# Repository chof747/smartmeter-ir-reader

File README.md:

## Smartmeter IR Reader/Writer

This is an implementation of the smart reader concept created by [volkszaehler.org](https://wiki.volkszaehler.org/hardware/controllers/ir-schreib-lesekopf-ttl-ausgang).

It has been modified as follows:

- Replaced 13k resistors by 10k (as I have a lot of them in stock)
- Added an RJ11 connector with 4 pins as a connector to the microcontroller unit

This board is intended to interface with a Microcontroller unit via an RJ11 connector.

## Schematic & Board Layout

## Revision History:
- **v1.0**: Initial version (Produced: 19.08.2023; not assembled)
- **v1.1**: Corrected RJ11 socket connector (Produced: 19.09.2023; First Assembly: 06.10.2023))
- **v1.2**: Corrected misorientation of Q1/Q2 transistor pins, Board cutout and added Pin descriptions (Produced 15.10.2023; Asembled: 10.11.2023 - successfully)

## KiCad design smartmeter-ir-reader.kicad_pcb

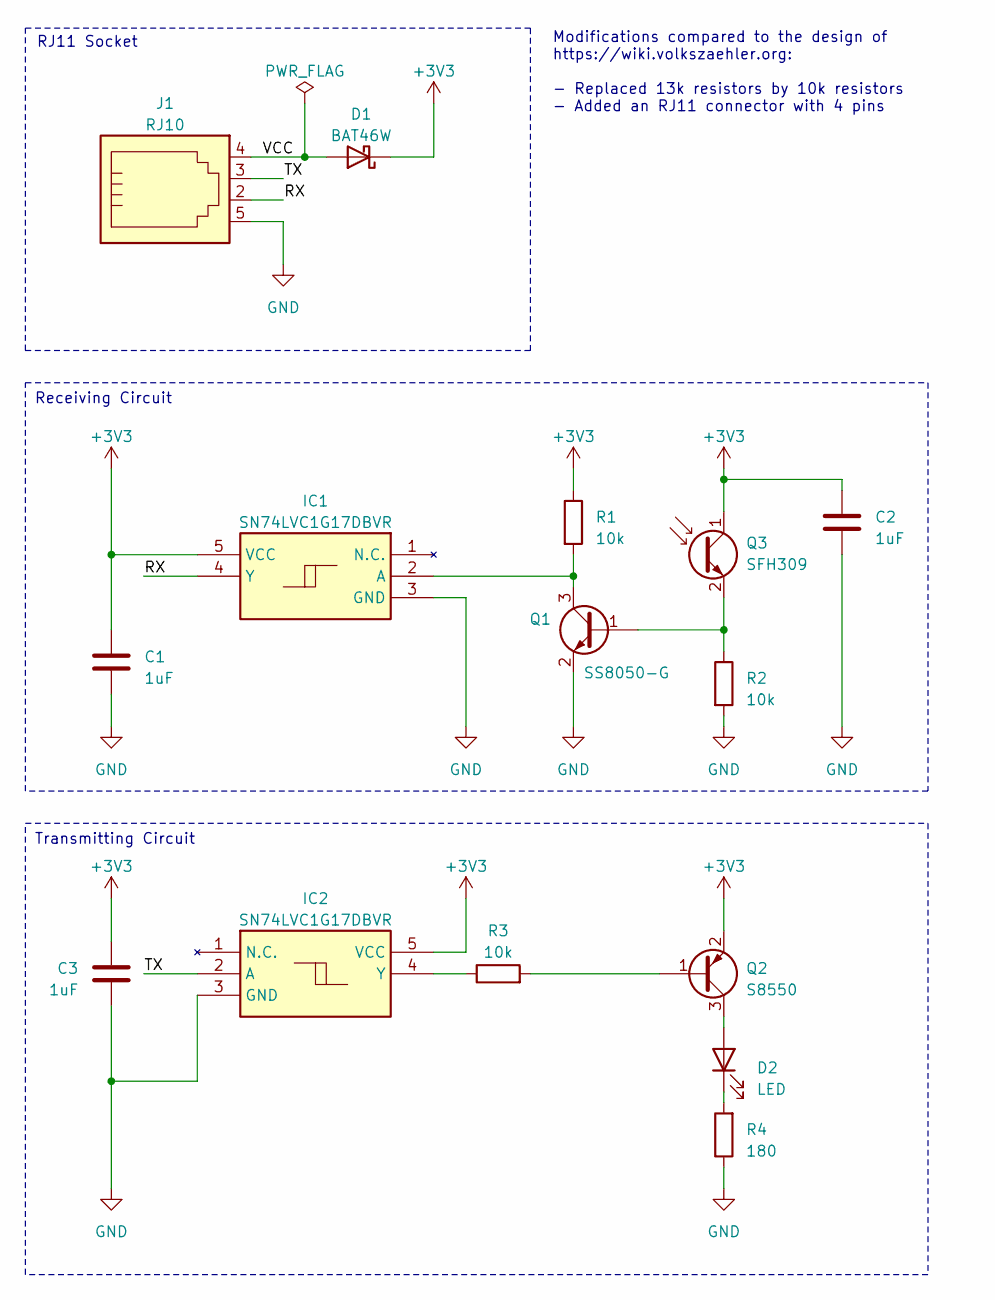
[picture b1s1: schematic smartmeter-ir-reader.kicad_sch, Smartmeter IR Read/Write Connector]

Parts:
C1, C2, C3: 1uF; C_0603_1608Metric_Pad1.08x0.95mm_HandSolder
D1: BAT46W; D_SOD-123
D2: LED; LED_D3.0mm_Clear
IC1, IC2: SN74LVC1G17DBVR; SOT95P270X145-5N; Manufacturer_Part_Number SN74LVC1G17DBVR; Mouser Part Number 595-SN74LVC1G17DBVR
J1: RJ10; RJ12_Amphenol_54601
Q1: SS8050-G; SOT-23
Q2: S8550; SOT-23
Q3: SFH309; LED_D3.0mm_Clear
R1, R2, R3: 10k; R_0603_1608Metric_Pad0.98x0.95mm_HandSolder
R4: 180; R_0603_1608Metric_Pad0.98x0.95mm_HandSolder

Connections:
+3V3: C1.1, C2.1, C3.1, D1.1 (K), IC1.5 (VCC), IC2.5 (VCC), Q2.2 (E), Q3.1 (C), R1.1
/RX: IC1.4 (Y), J1.2
/TX: IC2.2 (A), J1.3
/VCC: D1.2 (A), J1.4
GND: C1.2, C2.2, C3.2, IC1.3 (GND), IC2.3 (GND), J1.5, Q1.2 (E), R2.2, R4.1
unnamed: D2.2 (A), Q2.3 (C)
unnamed: D2.1 (K), R4.2
unnamed: IC1.2 (A), Q1.3 (C), R1.2
unnamed: IC2.4 (Y), R3.1
unnamed: Q1.1 (B), Q3.2 (E), R2.1
unnamed: Q2.1 (B), R3.2

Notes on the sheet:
Receiving Circuit
Transmitting Circuit
Modifications compared to the design of https://wiki.volkszaehler.org: - Replaced 13k resistors by 10k resistors - Added an RJ11 connector with 4 pins
RJ11 Socket

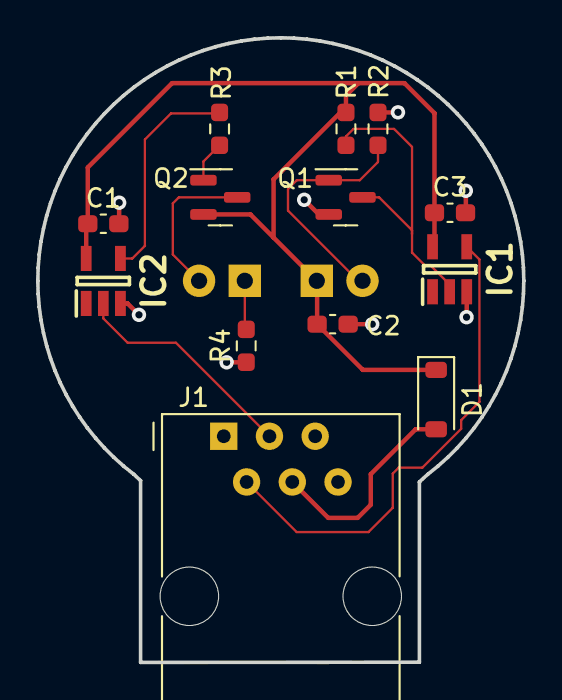
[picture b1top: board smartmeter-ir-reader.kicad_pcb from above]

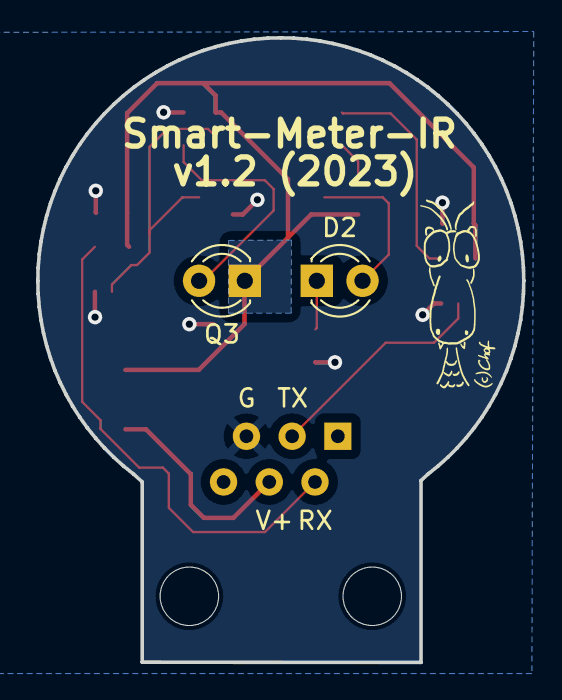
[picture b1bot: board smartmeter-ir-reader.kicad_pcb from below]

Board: 2 copper layers, 27.0 x 34.7 mm, 15 parts (2 on the bottom side), 11 nets.

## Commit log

2023-07-28 Initial commit including docs for volkszaehler pcb and schematics
2023-08-03 Initial version
2023-08-19 Initial version Revision 1.0
2023-09-15 corrected RJ12 socket Connector
2023-10-06 First Assembly
2023-10-11 Reformatted schematic
2023-10-11 Added board drawings to readme
2023-10-15 V1.2 with corrected transistor layouts
2023-11-13 successfully corrected transistor fix and assembled
2024-02-10 added board outline
